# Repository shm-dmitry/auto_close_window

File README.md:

This project allows auto-open and auto-close your windows.
Project consists schematics of 3 modules and firmware for 2 controllers

Project re-started

In-door modules:
==============

1. Placed on window neare handle. It controls handle state (via hall sensor and magnet) and allows to you to push button open or close manually
Also this module connected to WIFI and allows to to control your window from any smart house server (via MQTT protocol).
2. Placed on up-side window frame. Contains servo, receives commands from module#1 and executes it.

Out-door module:
==============

1. Listen for a noise and check air quality. 

Project status
==============

| Hardware | status |
| ---- | ---- |
| Indoor schema :: near-handle module | no |
| Indoor schema :: servo module | no |
| Indoor schema :: digital channel to outdoor schema | no |
| Outdoor module schema :: microcontroller and its periphery | no |
| Outdoor module schema :: sensors | no |

| Board | status |
| ---- | ---- |
| Indoor board :: near-handle module | no |
| Indoor board :: servo module | no |
| Outdoor module board | no |

| Firmware | status |
| ---- | ---- |
| Indoor firmware :: hardware sensors - hall, switch and soft lock | no |
| Indoor firmware :: buttons | no |
| Indoor firmware :: servo control and calibration | no |
| Indoor firmware :: led indication | no |
| Indoor firmware :: controller | no |
| Outdoor firmware :: BMP280 | no |
| Outdoor firmware :: SGP30 | no |
| Outdoor firmware :: Noise sensor | no |
| Outdoor firmware :: Sensor value filters and controller | no |
| Outdoor firmware :: Data transmitter | no |

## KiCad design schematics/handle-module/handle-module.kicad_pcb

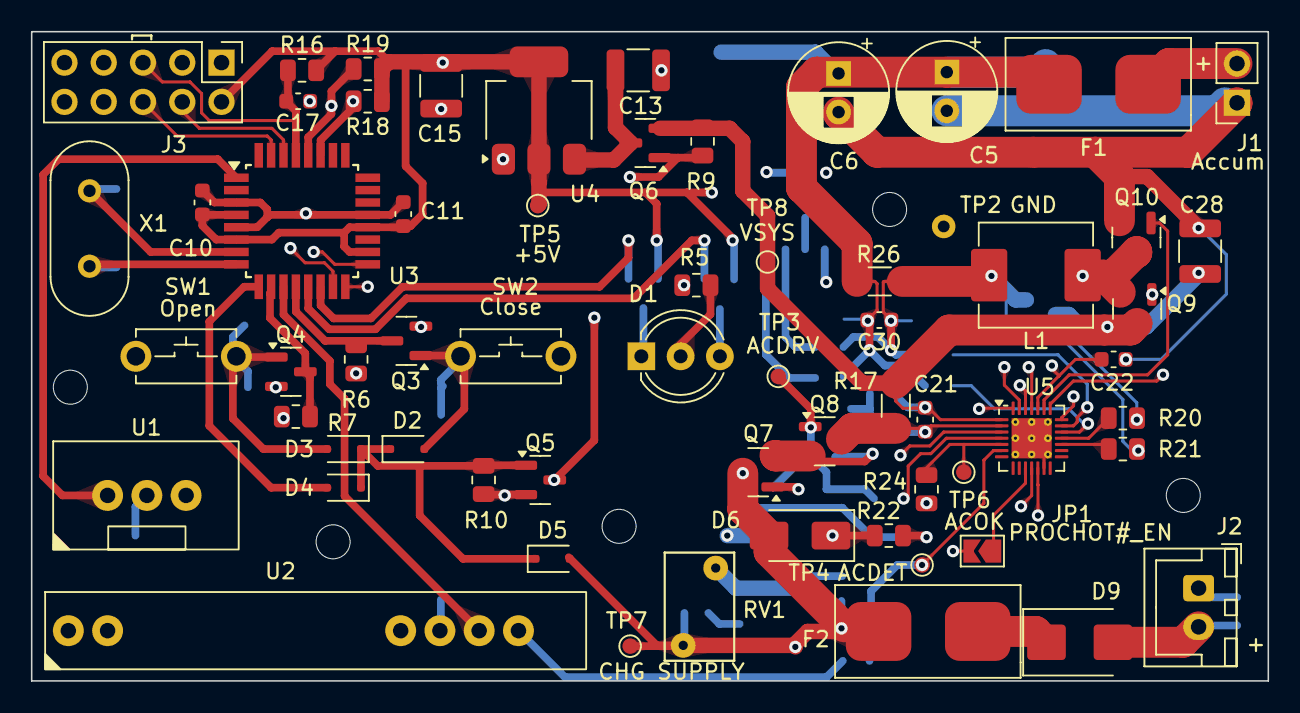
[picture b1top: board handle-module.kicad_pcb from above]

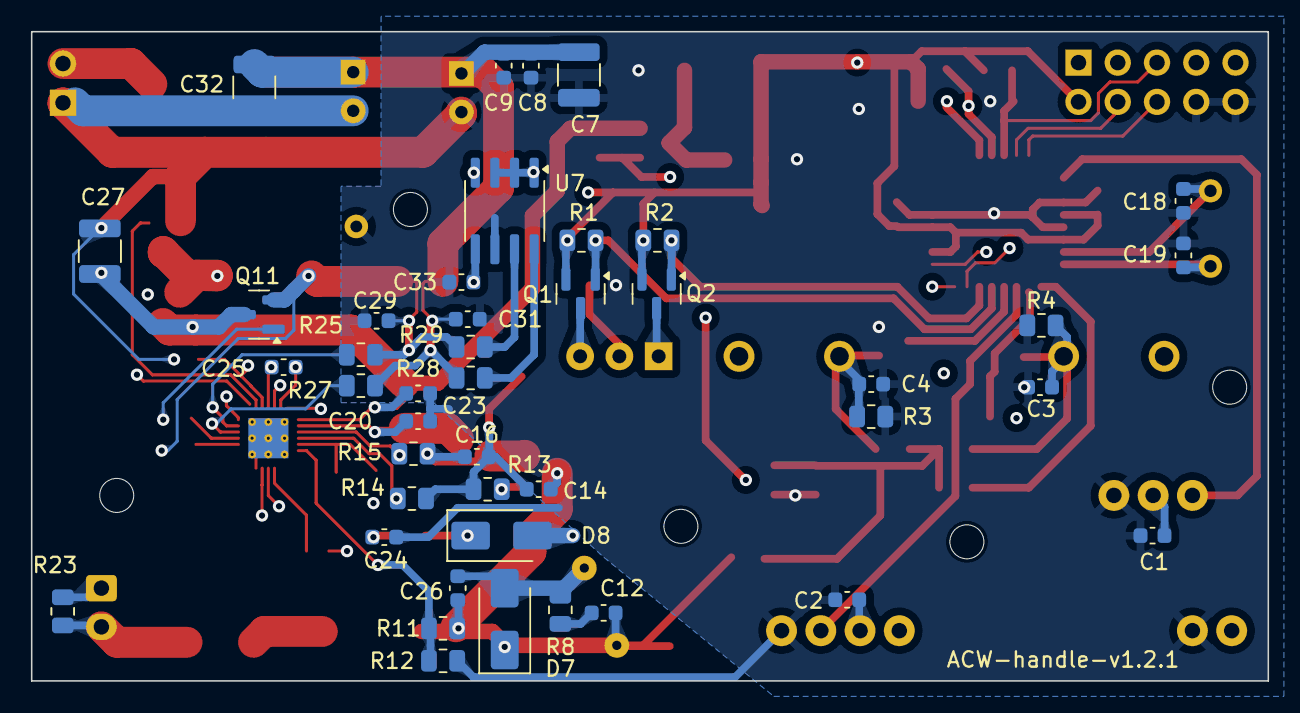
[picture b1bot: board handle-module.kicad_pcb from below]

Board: 4 copper layers, 80.0 x 42.0 mm, 114 parts (43 on the bottom side), 61 nets.

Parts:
C1, C2, C8, C12, C22, C24: 2.2 uF; C_0603_1608Metric
C3, C4, C9, C10, C11, C17, C20, C21, C23, C29, C30, C31, C33: 100 nF; C_0603_1608Metric
C5, C6: 100 uF; CP_Radial_D6.3mm_P2.50mm
C7, C13, C15, C27, C28, C32: 22 uF; C_1210_3225Metric
C14: 1 nF; C_0603_1608Metric
C16, C25: 47 nF; C_0603_1608Metric
C18, C19: 15 pF; C_0603_1608Metric
C26: 4.7 uF; C_0603_1608Metric
D1: red/green, common cathode, F3; LED_D5.0mm-3
D2, D3, D4, D5: BAT760; D_SOD-323F
D6, D8: 15MQ030NPBF; D_SMA
D7: SMAJ26A; D_SMA
D9: ES2J; D_SMB
F1, F2: 3A; FuseHolder1808
H1, H2, H3, H4, H5: MountingHole; MountingHole_2.2mm_M2
J1: 2*LiFePo4@18650@1800mAh, 6,4V; PinSocket_1x02_P2.54mm_Vertical
J2: Charger; JST_XH_B2B-XH-A_1x02_P2.50mm_Vertical
J3: USBASP; PinHeader_2x05_P2.54mm_Vertical
JP1: PROCHOT#_EN; SolderJumper-2_P1.3mm_Open_TrianglePad1.0x1.5mm
L1: AMPLF0630, 8,2uH; L_Abracon_ASPI-0630LR
NT1: AGND/PGND; NetTie-2_SMD_Pad2.0mm
NT2, NT3: NetTie_2; NetTie-2_SMD_Pad0.5mm
Q1, Q2, Q6: IRLML5203; SOT-23
Q3, Q4, Q5, Q7, Q8, Q9, Q10, Q11: IRLML0030; SOT-23
R1, R2, R3, R4, R6, R7, R9, R10, R16, R18, R19, R24: 10K; R_0805_2012Metric
R5: 620; R_0805_2012Metric
R8: 5R; R_0805_2012Metric
R11: 100K; R_0805_2012Metric
R12: 45K; R_0805_2012Metric
R13: 5; R_0805_2012Metric
R14, R15: 3K9; R_0805_2012Metric
R17, R26: 0.01 R; R_1206_3216Metric
R20: 3K3; R_0805_2012Metric
R21, R22, R25, R27, R28, R29: 10; R_0805_2012Metric
R23: 2K2; R_0805_2012Metric
RV1: JVR-05N180M; RV_Disc_D7mm_W4.5mm_P5mm
SW1, SW2: KLS7-TS3601-5.0-180; SW_PUSH_P6.5_W3.5
TP2: GND; TestPoint_Plated_Hole_D1.0mm
TP3: ACDRV; TestPoint_Pad_D1.0mm
TP4: ACDET; TestPoint_Pad_D1.0mm
TP5: +5V; TestPoint_Pad_D1.0mm
TP6: ACOK; TestPoint_Pad_D1.0mm
TP7: CHG SUPPLY; TestPoint_Pad_D1.0mm
TP8: VSYS; TestPoint_Pad_D1.0mm
U1: STX882@443MHz; STX882_Vertical
U2: SRX882@443MHz; SRX882_Vertical
U3: ATmega328-A; TQFP-32_7x7mm_P0.8mm
U4: AMS1117-5.0; SOT-223-3_TabPin2
U5: BQ24780S; QFN-28-1EP_4x4mm_P0.4mm_EP2.6x2.6mm_ThermalVias
U7: INA219; SOIC-8_3.9x4.9mm_P1.27mm
X1: HC-49U, 8MHz; Crystal_HC49-U_Vertical

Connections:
+5V: C1.1, C2.1, C10.1, C11.1, C15.1, C33.1, J3.2, Q1.2 (S), Q2.2 (S), R1.2, R2.2, R6.2, R7.2, R16.2, R18.1, R19.1, R24.2, TP5.1, U1.3 (VCC), U2.3 (VCC), U2.4 (CS), U3.4 (VCC), U3.6 (VCC), U3.18 (AVCC), U3.20 (AREF), U4.2 (VO), U7.5 (VCC)
/CHARGER_BATDRV: Q11.1 (G), R20.1
/CHARGER_BATSRC: C29.1, C30.1, L1.2, NT2.2, Q11.2 (S), R21.1, R26.1
/CHARGER_SRN: NT3.1, R27.1, R28.1
/CHARGER_SRP: NT2.1, R25.2, R29.2
/CHARGER_SUPPLY: C12.1, C14.1, C26.1, D5.2 (A), D6.2 (A), D7.1 (A1), F2.2, Q7.3 (D), R11.1, RV1.1, TP7.1
/CHR_VSYS_NMOS: C16.1, Q7.2 (S), Q8.2 (S), R15.1
/CLOSE_BUTTON: C4.2, D2.2 (A), Q3.1 (G), R3.1, SW2.1
/CLOSE_BUTTON_5V#: Q3.3 (D), R6.1, U3.12 (PB0)
/FM_IN: U2.5 (DATA), U3.11 (PD7)
/FM_OUT: U1.2 (DATA), U3.1 (PD3)
/IC_POWER_UP: D4.2 (A), U3.9 (PD5)
/LED_GREEN#: Q1.1 (G), R1.1, U3.13 (PB1)
/LED_RED#: Q2.1 (G), R2.1, U3.14 (PB2)
/MISO: J3.9, U3.16 (PB4)
/MOSI: J3.1, U3.15 (PB3)
/OPEN_BUTTON: C3.2, D3.2 (A), Q4.1 (G), R4.1, SW1.2
/OPEN_BUTTON_5V#: Q4.3 (D), R7.1, U3.10 (PD6)
/PROCHOT#: JP1.2 (B), Q5.3 (D), Q6.1 (G), R9.2
/RESET#: C17.1, J3.5, R16.1, U3.29 (~RESET/PC6)
/RXD: J3.4, U3.30 (PD0)
/SCK: J3.7, U3.17 (PB5)
/SCL: R19.2, U3.28 (PC5), U5.12 (SCL), U7.4 (SCL)
/SDA: R18.2, U3.27 (PC4), U5.11 (SDA), U7.1 (A1), U7.2 (A0), U7.3 (SDA)
/TXD: J3.6, U3.31 (PD1)
/VBAT: C5.1, C6.1, C7.1, C8.1, C9.2, C30.2, C31.1, C32.1, D8.2 (A), F1.2, NT3.2, R26.2, SW1.1, SW2.2
/VSYS: C21.2, C23.1, C27.1, C28.1, Q6.2 (S), Q9.3 (D), Q11.3 (D), R9.1, R17.2, TP8.1, U5.1 (ACN)
GNDA: C1.2, C2.2, C3.1, C4.1, C6.2, C7.2, C8.2, C9.1, C10.2, C11.2, C13.2, C15.2, C17.2, C18.2, C19.2, C20.2, C23.2, C24.2, C29.2, C31.2, C33.2, J3.8, J3.10, NT1.2, Q3.2 (S), Q4.2 (S), Q5.2 (S), R3.2, R4.2, R5.2, R10.2, R12.2, TP2.1, U1.4 (GND), U2.2 (GND), U2.6 (GND), U3.3 (GND), U3.5 (GND), U3.21 (GND), U4.1 (GND), U5.22 (AGND), U7.6 (GND)
GNDPWR: C5.2, C22.2, C26.2, C27.2, C28.2, C32.2, D7.2 (A2), J1.1, J2.1, NT1.1, Q10.2 (S), R8.2, R23.2, RV1.2, U5.13 (CMPIN), U5.29 (PGND)
unnamed: C12.2, R8.1
unnamed: D1.1 (A1), Q2.3 (D)
unnamed: D1.3 (A2), Q1.3 (D)
unnamed: D1.2 (K), R5.1
unnamed: D2.1 (K), D3.1 (K), D4.1 (K), D5.1 (K), Q5.1 (G), R10.1
unnamed: D6.1 (K), D8.1 (K), R22.2
unnamed: D9.2 (A), J2.2, R23.1
unnamed: D9.1 (K), F2.1
unnamed: F1.1, J1.2
unnamed: JP1.1 (A), U5.10 (PROCHOT#)
unnamed: C13.1, Q6.3 (D), U4.3 (VI)
unnamed: Q7.1 (G), R13.1
unnamed: C20.1, C21.1, Q8.3 (D), R17.1, U5.2 (ACP)
unnamed: C14.2, C16.2, Q8.1 (G), R13.2, R14.1, TP3.1
unnamed: Q9.1 (G), U5.26 (HIDRV)
unnamed: C25.2, L1.1, Q9.2 (S), Q10.3 (D), U5.27 (PHASE)
unnamed: Q10.1 (G), U5.23 (LODRV)
unnamed: C18.1, U3.7 (XTAL1/PB6), X1.2
unnamed: C19.1, U3.8 (XTAL2/PB7), X1.1
unnamed: R11.2, R12.1, TP4.1, U5.6 (ACDET)
unnamed: R14.2, U5.4 (ACDRV)
unnamed: R24.1, TP6.1, U5.5 (ACOK)
unnamed: R20.2, U5.18 (BATDRV)
unnamed: R21.2, U5.17 (BATSRC)
unnamed: C25.1, U5.25 (BTST)
unnamed: R15.2, U5.3 (CMSRC)
unnamed: C22.1, U5.21 (ILIM), U5.24 (REGN)
unnamed: R27.2, U5.19 (SRN)
unnamed: R25.1, U5.20 (SRP)
unnamed: C24.1, R22.1, U5.28 (VCC)
unnamed: R28.2, U7.8 (VIN_+)
unnamed: R29.1, U7.7 (VIN_-)

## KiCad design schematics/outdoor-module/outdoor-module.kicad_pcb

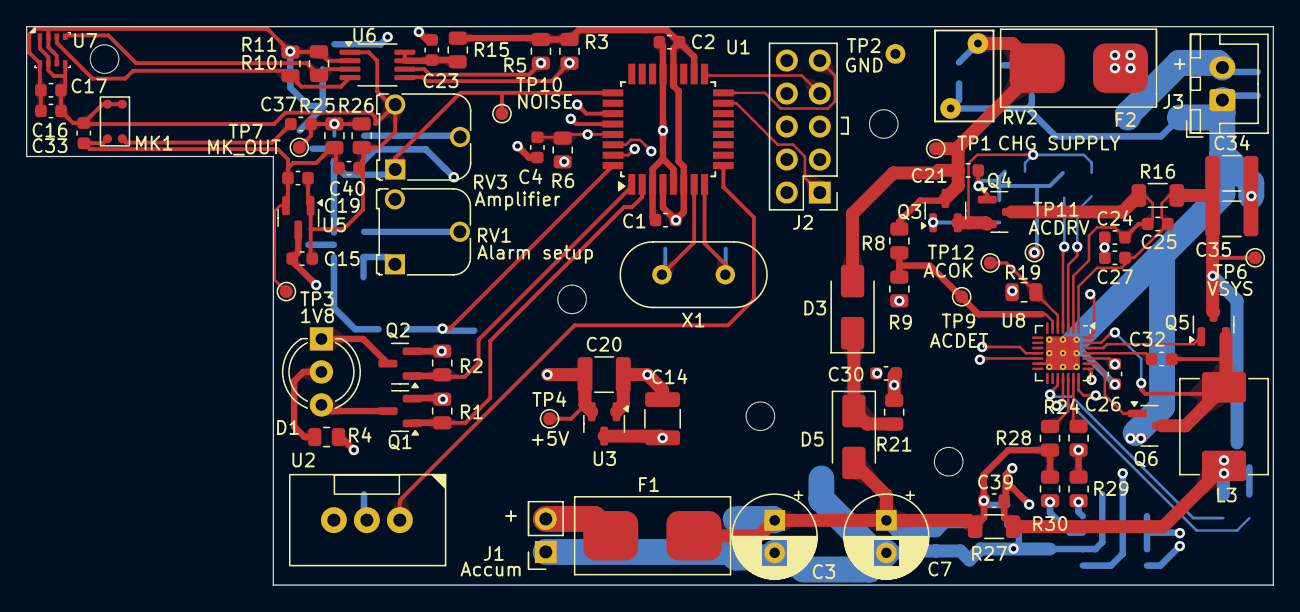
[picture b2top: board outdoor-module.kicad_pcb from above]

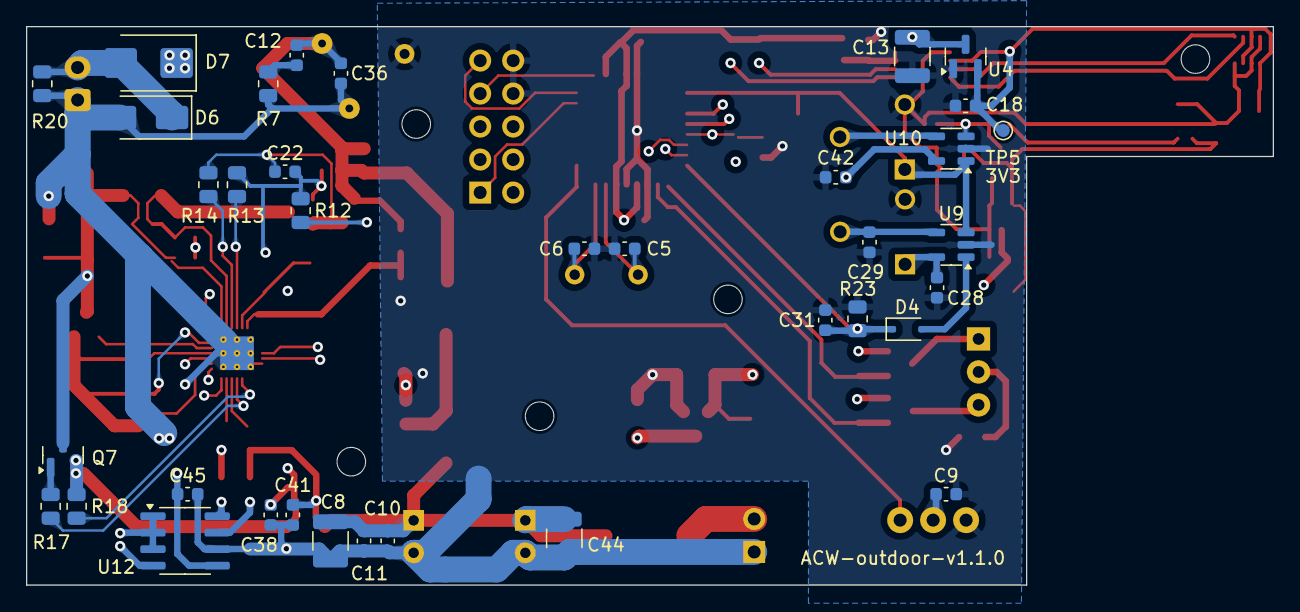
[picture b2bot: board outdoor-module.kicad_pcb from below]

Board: 4 copper layers, 96.0 x 43.0 mm, 127 parts (37 on the bottom side), 63 nets.

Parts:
C1, C2, C4, C9, C11, C16, C17, C24, C25, C27, C28, C29, C31, C33, C37, C38, C39, C40, C41, C42, C45: 100 nF; C_0603_1608Metric
C3, C7: 100 uF; CP_Radial_D6.3mm_P2.50mm
C5, C6: 15 pF; C_0603_1608Metric
C8, C13, C14, C20, C34, C35, C44: 22 uF; C_1210_3225Metric
C10, C15, C18, C19, C30: 1 uF; C_0603_1608Metric
C12, C26: 2.2 uF; C_0603_1608Metric
C21: 1 nF; C_0603_1608Metric
C22, C32: 47 nF; C_0603_1608Metric
C23: 200 pF; C_0603_1608Metric
C36: 4.7 uF; C_0603_1608Metric
D1: red/green, common cathode, F3; LED_D5.0mm-3
D3, D5: 15MQ030NPBF; D_SMA
D4: BAV21WS; D_SOD-323F
D6: SMAJ26A; D_SMA
D7: ES2J; D_SMB
F1, F2: 3A; FuseHolder1808
H1, H2, H3, H4, H5: MountingHole; MountingHole_2.2mm_M2
J1: 2*LiFePo4@18650@1800mAh, 6,4V; PinSocket_1x02_P2.54mm_Vertical
J2: USBASP; PinHeader_2x05_P2.54mm_Vertical
J3: Charger; JST_XH_B2B-XH-A_1x02_P2.50mm_Vertical
L3: AMPLF0630, 8,2uH; L_Abracon_ASPI-0630LR
MK1: VSM3729AT-GL9-A30; SMD03722C4
NT1: AGND/PGND; NetTie-2_SMD_Pad2.0mm
NT2, NT3: NetTie_2; NetTie-2_SMD_Pad0.5mm
Q1, Q2: IRLML5203; SOT-23
Q3, Q4, Q5, Q6, Q7: IRLML0030; SOT-23
R1, R2, R6, R19: 10K; R_0805_2012Metric
R3, R5, R10, R11: 4K7; R_0805_2012Metric
R4: 1K; R_0805_2012Metric
R7: 2; R_0805_2012Metric
R8, R23, R25, R26: 100K; R_0805_2012Metric
R9: 45K; R_0805_2012Metric
R12: 4R7; R_0805_2012Metric
R13, R14, R17: 4K; R_0805_2012Metric
R15: 200K; R_0805_2012Metric
R16, R27: 0.01 R; R_1206_3216Metric
R18, R21, R24, R28, R29, R30: 10; R_0805_2012Metric
R20: 2K2; R_0805_2012Metric
RV1, RV3: RM065, 100K; Potentiometer_Runtron_RM-065_Vertical
RV2: JVR-05N180M; RV_Disc_D7mm_W4.5mm_P5mm
TP1: CHG SUPPLY; TestPoint_Pad_D1.0mm
TP2: GND; TestPoint_Plated_Hole_D1.0mm
TP3: 1V8; TestPoint_Pad_D1.0mm
TP4: +5V; TestPoint_Pad_D1.0mm
TP5: 3V3; TestPoint_Pad_D1.0mm
TP6: VSYS; TestPoint_Pad_D1.0mm
TP7: MK_OUT; TestPoint_Pad_D1.0mm
TP9: ACDET; TestPoint_Pad_D1.0mm
TP10: NOISE; TestPoint_Pad_D1.0mm
TP11: ACDRV; TestPoint_Pad_D1.0mm
TP12: ACOK; TestPoint_Pad_D1.0mm
U1: ATmega328-A; TQFP-32_7x7mm_P0.8mm
U2: STX882@315MHz; STX882_Vertical
U3: MCP1703T-5002E; SOT-23
U4: MCP1703T-3302E; SOT-23
U5: MCP1703T-1802E; SOT-23
U6: PCA9306; MSOP-8_3x3mm_P0.65mm
U7: BME280; Bosch_LGA-8_2.5x2.5mm_P0.65mm_ClockwisePinNumbering
U8: BQ24780S; QFN-28-1EP_4x4mm_P0.4mm_EP2.6x2.6mm_ThermalVias
U9, U10: AD8541; SOT-23-5
U12: INA219; SOIC-8_3.9x4.9mm_P1.27mm
X1: HC-49U, 8MHz; Crystal_HC49-U_Vertical

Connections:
+1V8: C19.1, C33.1, C40.1, MK1.1 (VCC), R25.1, TP3.1, U5.2 (VO)
+3V3: C16.1, C17.1, C18.2, R10.1, R11.1, TP5.1, U4.2 (VO), U6.2 (VREF1), U7.2 (CSB), U7.6 (VDDIO), U7.8 (VDD)
+5V: C1.1, C2.1, C9.1, C13.1, C15.1, C20.1, C28.1, C42.1, C45.1, J2.2, Q1.2 (S), Q2.2 (S), R1.2, R2.2, R3.1, R5.1, R6.2, R15.1, R19.2, RV1.1, TP4.1, U1.4 (VCC), U1.6 (VCC), U1.18 (AVCC), U1.20 (AREF), U2.3 (VCC), U3.2 (VO), U4.3 (VI), U5.3 (VI), U9.5 (V+), U10.5 (V+), U12.5 (VCC)
/CHARGER_BATDRV: Q7.1 (G), R17.1
/CHARGER_BATSRC: C38.1, C39.1, L3.2, NT2.2, Q7.2 (S), R18.1, R27.1
/CHARGER_DONE#: Q1.1 (G), R1.1, U1.2 (PD4)
/CHARGER_IN_PROGRESS#: Q2.1 (G), R2.1, U1.1 (PD3)
/CHARGER_SRN: NT3.1, R28.1, R30.1
/CHARGER_SRP: NT2.1, R24.1, R29.2
/CHARGER_SUPPLY: C12.1, C21.1, C36.1, D3.2 (A), F2.2, Q3.3 (D), R8.1, RV2.1, TP1.1
/FM_OUT: U1.9 (PD5), U2.2 (DATA)
/MISO: J2.9, U1.16 (PB4)
/MOSI: J2.1, U1.15 (PB3)
/NOISE: RV3.1, TP10.1, U1.25 (PC2), U9.3 (Vin+), U10.1 (OUT)
/NOISE_ALARM: C31.1, D4.1 (K), R23.1, U1.32 (PD2)
/RESET#: C4.1, J2.5, R6.1, U1.29 (~RESET/PC6)
/RXD: J2.4, U1.30 (PD0)
/SCK: J2.7, U1.17 (PB5)
/SCL: R5.2, U1.28 (PC5), U6.6 (SCL2), U8.12 (SCL), U12.4 (SCL)
/SCL_3V3: R10.2, U6.3 (SCL1), U7.4 (SCK)
/SDA: R3.2, U1.27 (PC4), U6.5 (SDA2), U8.11 (SDA), U12.1 (A1), U12.2 (A0), U12.3 (SDA)
/SDA_3V3: R11.2, U6.4 (SDA1), U7.3 (SDI)
/TXD: J2.6, U1.31 (PD1)
/VBAT: C3.1, C7.1, C8.1, C10.1, C11.2, C39.2, C41.1, C44.1, D5.2 (A), F1.2, NT3.2, R27.2
/VSYS: C14.1, C25.2, C27.1, C34.1, C35.1, Q5.3 (D), Q7.3 (D), R16.2, TP6.1, U3.3 (VI), U8.1 (ACN)
GNDA: C1.2, C2.2, C4.2, C5.2, C6.2, C7.2, C8.2, C9.2, C10.2, C11.1, C13.2, C14.2, C15.2, C16.2, C17.2, C18.1, C19.2, C20.2, C23.1, C24.2, C27.2, C28.2, C29.2, C30.2, C31.2, C33.2, C38.2, C40.2, C41.2, C42.2, C45.2, J2.8, J2.10, MK1.2 (GND), MK1.3 (GND), NT1.2, R4.2, R9.2, R23.2, R26.2, RV1.3, RV3.3, TP2.1, U1.3 (GND), U1.5 (GND), U1.21 (GND), U2.4 (GND), U3.1 (GND), U4.1 (GND), U5.1 (GND), U6.1 (GND), U7.1 (GND), U7.5 (SDO), U7.7 (GND), U8.22 (AGND), U9.2 (GND), U10.2 (GND), U12.6 (GND)
GNDPWR: C3.2, C26.2, C34.2, C35.2, C36.2, C44.2, D6.2 (A2), J1.1, J3.1, NT1.1, Q6.2 (S), R7.2, R20.2, RV2.2, U8.13 (CMPIN), U8.29 (PGND)
unnamed: C12.2, R7.1
unnamed: D1.1 (A1), Q2.3 (D)
unnamed: D1.3 (A2), Q1.3 (D)
unnamed: D1.2 (K), R4.1
unnamed: D3.1 (K), D5.1 (K), R21.2
unnamed: D4.2 (A), U9.1 (OUT)
unnamed: D6.1 (A1), D7.2 (A), J3.2, R20.1
unnamed: D7.1 (K), F2.1
unnamed: F1.1, J1.2
unnamed: C37.1, MK1.4 (OUT)
unnamed: Q3.1 (G), R12.1
unnamed: C22.1, Q3.2 (S), Q4.2 (S), R14.1
unnamed: C24.1, C25.1, Q4.3 (D), R16.1, U8.2 (ACP)
unnamed: C21.2, C22.2, Q4.1 (G), R12.2, R13.1, TP11.1
unnamed: Q5.1 (G), U8.26 (HIDRV)
unnamed: C32.2, L3.1, Q5.2 (S), Q6.3 (D), U8.27 (PHASE)
unnamed: Q6.1 (G), U8.23 (LODRV)
unnamed: C5.1, U1.7 (XTAL1/PB6), X1.2
unnamed: C6.1, U1.8 (XTAL2/PB7), X1.1
unnamed: C23.2, R15.2, U6.7 (VREF2), U6.8 (EN)
unnamed: R8.2, R9.1, TP9.1, U8.6 (ACDET)
unnamed: R13.2, U8.4 (ACDRV)
unnamed: R19.1, TP12.1, U8.5 (ACOK)
unnamed: R17.2, U8.18 (BATDRV)
unnamed: R18.2, U8.17 (BATSRC)
unnamed: C32.1, U8.25 (BTST)
unnamed: R14.2, U8.3 (CMSRC)
unnamed: C26.1, U8.21 (ILIM), U8.24 (REGN)
unnamed: R28.2, U8.19 (SRN)
unnamed: R24.2, U8.20 (SRP)
unnamed: C30.1, R21.1, U8.28 (VCC)
unnamed: C29.1, RV1.2, U9.4 (Vin-)
unnamed: C37.2, R25.2, R26.1, TP7.1, U10.3 (Vin+)
unnamed: RV3.2, U10.4 (Vin-)
unnamed: R29.1, U12.8 (VIN_+)
unnamed: R30.2, U12.7 (VIN_-)

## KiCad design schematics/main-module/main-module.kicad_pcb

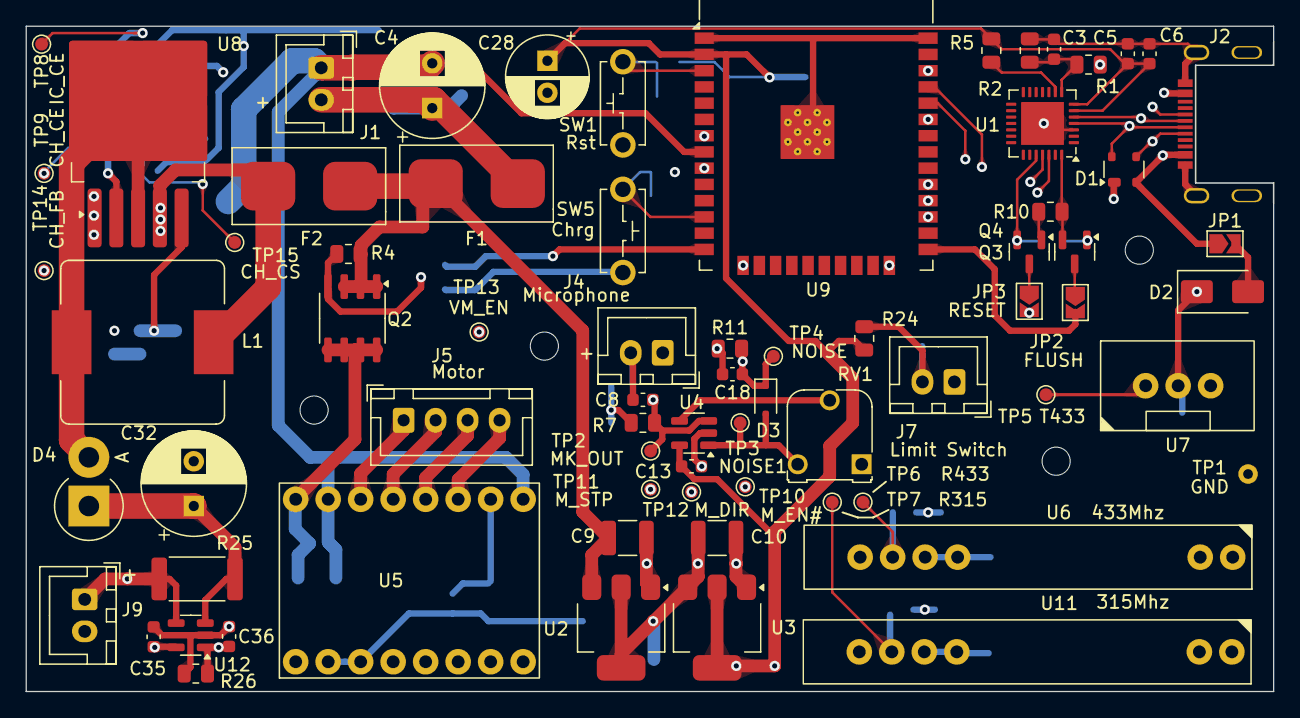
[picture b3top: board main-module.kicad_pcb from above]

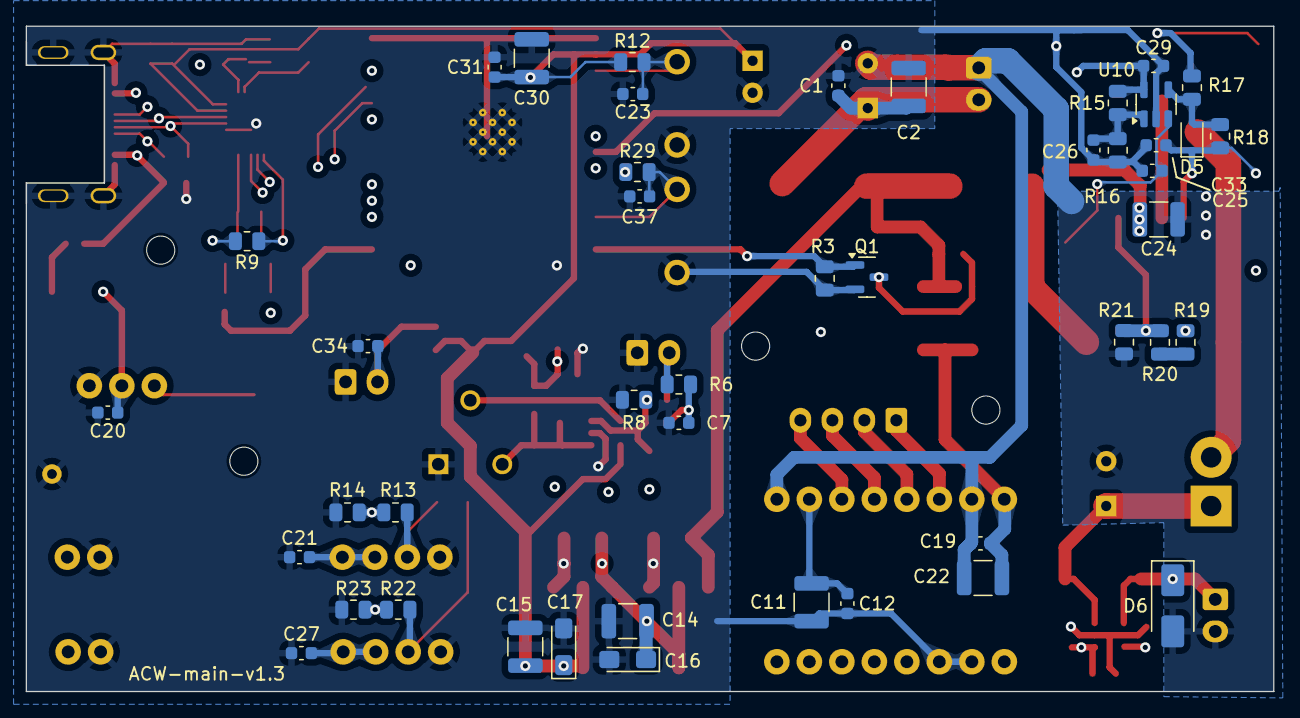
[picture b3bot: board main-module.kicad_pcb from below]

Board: 4 copper layers, 97.5 x 52.0 mm, 121 parts (45 on the bottom side), 55 nets.

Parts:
C1, C12, C19, C20, C21, C27, C31: 4.7 uF; C_0603_1608Metric
C2, C9, C10, C11, C14, C15, C22, C24, C30: 22 uF; C_1210_3225Metric
C3, C5, C6, C33: 10 uF; C_0603_1608Metric
C4: 1000 uF; CP_Radial_D8.0mm_P3.50mm
C7, C13, C29, C35: 100 nF; C_0603_1608Metric
C8: 47 nF; C_0603_1608Metric
C16, C17: 22 uF; CP_EIA-3216-10_Kemet-I_Pad1.58x1.35mm_HandSolder
C18: 1 uF; C_0603_1608Metric
C23, C34, C37: 330 nF; C_0603_1608Metric
C25, C26, C36: 10 nF; C_0603_1608Metric
C28: 100 uF; CP_Radial_D6.3mm_P2.50mm
C32: 220 uF@35V; CP_Radial_D8.0mm_P3.50mm
D1: SP0503BAHT; SOT-143
D2: US1M; D_SMA
D3, D5: BAV21WS; D_SOD-323F
D4: SR540; D_DO-201AD_P3.81mm_Vertical_AnodeUp
D6: SMAJ26A; D_SMA
F1: 6A; FuseHolder1808
F2: 3A; FuseHolder1808
H1, H2, H3, H4: MountingHole; MountingHole_2.2mm_M2
J1: Conn_01x02_Socket; JST_XH_B2B-XH-A_1x02_P2.50mm_Vertical
J2: USB_C_Receptacle_USB2.0; USB_C_P16_MIDMOUNT_1.6
J4: Microphone; JST_XH_B2B-XH-A_1x02_P2.50mm_Vertical
J5: Conn_01x04_Socket; JST_XH_B4B-XH-A_1x04_P2.50mm_Vertical
J7: Limit Switch; JST_XH_B2B-XH-A_1x02_P2.50mm_Vertical
J9: Charger port; JST_XH_B2B-XH-A_1x02_P2.50mm_Vertical
JP1: Charge from flusher; SolderJumper-2_P1.3mm_Open_TrianglePad1.0x1.5mm
JP2: FLUSH; SolderJumper-2_P1.3mm_Open_TrianglePad1.0x1.5mm
JP3: RESET; SolderJumper-2_P1.3mm_Open_TrianglePad1.0x1.5mm
L1: AMPLF1260, 4.7 uH; L_TaiTech_TMPC1265_13.5x12.5mm
NT1: AGND/PGND; NetTie-2_SMD_Pad2.0mm
Q1: IRLML0030; SOT-23
Q2: IRF7425PbF; SOIC-8_3.9x4.9mm_P1.27mm
Q3, Q4: BC847; SOT-23
R1, R13, R22: 22K; R_0805_2012Metric
R2, R14, R23: 47K; R_0805_2012Metric
R3, R6, R8, R9, R10, R11, R15, R20, R24, R29: 10K; R_0805_2012Metric
R4, R5, R12, R19, R21: 1K; R_0805_2012Metric
R7: 20K; R_0805_2012Metric
R16: 200; R_0805_2012Metric
R17: 620; R_0805_2012Metric
R18: 200K; R_0805_2012Metric
R25: 0,5; R_2512_6332Metric
R26: 100K; R_0805_2012Metric
RV1: RM065, 100K; Potentiometer_Runtron_RM-065_Vertical
SW1, SW5: KLS7-TS3601-5.0-180; SW_PUSH_P6.5_W3.5
TP1: GND; TestPoint_Plated_Hole_D1.0mm
TP2: MK_OUT; TestPoint_Pad_D1.0mm
TP3: NOISE1; TestPoint_Pad_D1.0mm
TP4: NOISE; TestPoint_Pad_D1.0mm
TP5: T433; TestPoint_Pad_D1.0mm
TP6: R433; TestPoint_Pad_D1.0mm
TP7: R315; TestPoint_Pad_D1.0mm
TP8: IC_CE; TestPoint_Pad_D1.0mm
TP9: CH_CE; TestPoint_Pad_D1.0mm
TP10: M_EN#; TestPoint_Pad_D1.0mm
TP11: M_STP; TestPoint_Pad_D1.0mm
TP12: M_DIR; TestPoint_Pad_D1.0mm
TP13: VM_EN; TestPoint_Pad_D1.0mm
TP14: CH_FB; TestPoint_Pad_D1.0mm
TP15: CH_CS; TestPoint_Pad_D1.0mm
U1: CP2102N-Axx-xQFN28; QFN-28-1EP_5x5mm_P0.5mm_EP3.35x3.35mm
U2: AMS1117-5.0; SOT-223-3_TabPin2
U3: AMS1117-3.3; SOT-223-3_TabPin2
U4: AD8541; SOT-23-5
U5: TMC2209_Module; TMC2209
U6: SRX882@433Mhz; SRX882_Vertical
U7: STX882@433Mhz; STX882_Vertical
U8: XL6009; TO-263-5_TabPin3
U9: ESP32-WROOM-32
U10: TL331; SOT-23-5
U11: SRX882@315Mhz; SRX882_Vertical
U12: INA169; SOT-23-5

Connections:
+3V3: C5.1, C6.1, C11.2, C12.1, C13.1, C15.2, C17.1, C28.1, C30.2, C31.1, R5.2, R12.1, R24.1, R29.1, U1.6 (VDD), U1.7 (VREGIN), U3.2 (VO), U4.5 (V+), U5.15 (VIO), U9.2 (VDD)
+5V: C7.1, C10.2, C14.2, C16.1, C20.1, C21.1, C27.1, C29.1, C35.1, D2.1 (K), R6.2, R7.2, R15.2, U2.2 (VO), U3.3 (VI), U6.3 (VCC), U6.4 (CS), U7.3 (VCC), U10.5 (V+), U11.3 (VCC), U11.4 (CS), U12.5 (V+)
+7.5V: C9.2, F1.2, F2.1, Q2.1 (S), Q2.2 (S), Q2.3 (S), R4.1, U2.3 (VI)
/7.5V_BEFORE_FUSE: C1.1, C2.1, C4.1, F1.1, J1.2
/+7.5V_CHARGER_AFTER_FUSE: C24.2, F2.2, L1.2, U8.4 (VIN)
/CHARGER_CURRENT_SENCE: C25.2, C36.2, R26.2, TP15.1, U10.3 (+), U12.1
/CHARGER_ENABLE: C33.2, D5.1 (K), R18.1, TP9.1, U8.2 (EN)
/CHARGER_FEEDBACK: R20.1, R21.2, TP14.1, U8.5 (FB)
/CHARGER_START_BUTTON: C37.1, R29.2, SW5.1, U9.12 (IO27)
/D+: D1.4 (K), J2.A6 (D+), J2.B6 (D+), U1.4 (D+)
/D-: D1.3 (K), J2.A7 (D-), J2.B7 (D-), U1.5 (D-)
/ESP32_ENABLE: C23.1, JP3.2 (B), R12.2, SW1.2, U9.3 (EN)
/ESP32_FLUSH: JP2.2 (B), U9.25 (IO0)
/FM_IN_5V_315: R22.2, TP7.1, U11.5 (DATA)
/FM_IN_5V_433: R13.2, TP6.1, U6.5 (DATA)
/FM_IN_315: R22.1, R23.2, U9.33 (IO21)
/FM_IN_433: R13.1, R14.2, U9.29 (IO5)
/FM_OUT_433: TP5.1, U7.2 (DATA), U9.36 (IO22)
/IC_CHARGER_ENABLE: R17.2, TP8.1, U9.8 (IO32)
/LIMIT_SWITCH: C34.1, J7.2, R24.2, U9.9 (IO33)
/M_DIR: TP12.1, U5.8 (DIR), U9.27 (IO16)
/M_ENABLE#: TP10.1, U5.1 (ENABLE#), U9.24 (IO2)
/M_STEP: TP11.1, U5.7 (STEP), U9.28 (IO17)
/NOISE: C18.1, D3.1 (K), R11.2, TP4.1, U9.7 (IO35)
/RXD_3V3: U1.26 (TXD), U9.34 (RXD0/IO3)
/TXD_3V3: U1.25 (RXD), U9.35 (TXD0/IO1)
/VM_ENABLE: Q1.1 (G), R3.1, TP13.1, U9.14 (IO12)
GNDA: C1.2, C2.2, C3.2, C4.2, C5.2, C6.2, C7.2, C9.1, C10.1, C11.1, C12.2, C13.2, C14.1, C15.1, C16.2, C17.2, C18.2, C20.2, C21.2, C23.2, C25.1, C26.1, C27.2, C28.2, C29.2, C30.1, C31.2, C33.1, C34.2, C35.2, C36.1, C37.2, D1.1 (A), J2.A1 (GND), J2.A12 (GND), J2.B1 (GND), J2.B12 (GND), J2.S1 (SHIELD), J4.1, J7.1, NT1.2, Q1.2 (S), R2.2, R3.2, R8.1, R11.1, R14.1, R16.1, R23.1, R26.1, RV1.1, SW1.1, SW5.2, TP1.1, U1.3 (GND), U1.29 (GND), U2.1 (GND), U3.1 (GND), U4.2 (GND), U5.2 (MS1), U5.3 (MS2), U6.2 (GND), U6.6 (GND), U7.4 (GND), U9.1 (GND), U9.15 (GND), U9.38 (GND), U9.39 (GND), U10.2 (V-), U11.2 (GND), U11.6 (GND), U12.2 (GND)
GNDPWR: C19.1, C22.1, C24.1, C32.2, D6.2 (A2), J1.1, J9.2, NT1.1, R21.1, U5.10 (GND), U5.16 (GND), U8.1 (GND)
unnamed: D2.2 (A), JP1.2 (B)
unnamed: D3.2 (A), RV1.3, TP3.1, U4.1 (OUT)
unnamed: D4.2 (A), L1.1, U8.3 (SW)
unnamed: C32.1, D4.1 (K), R19.2, R25.1, U12.3 (+)
unnamed: D5.2 (A), R17.1, R18.2, U10.4
unnamed: D6.1 (A1), J9.1, R25.2, U12.4 (-)
unnamed: C8.1, J4.2, R6.1
unnamed: J5.1, U5.11 (M1B)
unnamed: J5.2, U5.12 (M1A)
unnamed: J5.3, U5.13 (M2A)
unnamed: J5.4, U5.14 (M2B)
unnamed: JP2.1 (A), Q3.3 (C)
unnamed: JP3.1 (A), Q4.3 (C)
unnamed: Q1.3 (D), Q2.4 (G), R4.2
unnamed: Q3.1 (B), R9.2
unnamed: Q3.2 (E), R10.1, U1.28 (~DTR)
unnamed: Q4.1 (B), R10.2
unnamed: Q4.2 (E), R9.1, U1.24 (~RTS)
unnamed: R19.1, R20.2
unnamed: C3.1, R1.2, R2.1, U1.8 (VBUS)
unnamed: R5.1, U1.9 (~RST)
unnamed: C8.2, R7.1, R8.2, TP2.1, U4.3 (Vin+)
unnamed: RV1.2, U4.4 (Vin-)
unnamed: C26.2, R15.1, R16.2, U10.1 (-)
VBUS: D1.2 (K), J2.A4 (VBUS), J2.A9 (VBUS), J2.B4 (VBUS), J2.B9 (VBUS), JP1.1 (A), R1.1
VD: C19.2, C22.2, Q2.5 (D), Q2.6 (D), Q2.7 (D), Q2.8 (D), U5.9 (VM)

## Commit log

2021-07-27 Continue working under schematics
2021-07-27 Added driver for servo FS5103B
2021-07-29 working under schematics
2021-08-03 1. working under schematics. 2. ESP32 firmware writen but not tested yet. 3. I conntected to ATMega controller and uploaded test firmware to it
2021-08-03 stop servo on full-open and full-close positions
2021-08-04 Start debugging process
2021-08-04 Indoor modules schematics and firmware works now!
2021-08-05 Preparing to debug ATMega controller. I have no JTAG, and USBasp does not allows debugging. I will try to use 443 MHZ transmitter and 433 Mhz receiver on raspberry pi as debug terminal :)
2021-08-08 Start writing firmware for outdoor module
2021-08-13 SGP30 Module works now
2021-08-13 I checked several pins_arduino.h, but only this works fine. Thanks to https://github.com/MCUdude/MightyCore
2021-08-13 Remove unused file
2021-08-17 actualized schematics of outdoor noise sensor module
2021-08-17 actualized some nominals in schematics
2021-08-22 BMP280 works now
2021-09-26 Changed Noise sensor schematics. Removed MSGEQ7 chip (replaced with program FFT). I cant find any live. Changed Volume Amplifier from transistors to chio.
2021-09-26 Noise sensor works
2021-09-27 added initially code for filter and encrypter components
2021-10-30 changed schematics. Removed 433MHZ transmitter. Outdoor module will transfer data using ESP32
2021-10-30 Added code to send data from AVR to ESP32
2021-10-30 Estabilished connection between AVR and ESP32. ESP32 ready to read data from AVR and send it into MQTT
2021-10-31 Change noise sensor schema
2021-11-04 changed microcontroller to ATMEGA328P to reduce device size
2021-11-04 Added TX and RX links from USBASP to ATMEGA
2021-11-04 Firmware and ATMega connection are synchronized. USBasp works successfully
2021-11-04 full schema on atmega328 tested and worked
2021-11-05 Start boards preparing - actualized new element dimentions
2021-11-05 Touch sensor are unstable. I made a decision to replace it by normally-open buttons
2021-11-06 Added button borders and nominals
2021-11-07 Start working under first border
2021-11-07 Board redesigned to reduce it width
2021-11-07 Indoor board - ready
2021-11-07 Indoor board - added ground polygon
2021-11-07 Start working under second border
2021-11-08 Servo module ready, but i will change connectors
2021-11-08 Servo module - added holes
2021-11-08 Added board for outdoor module
2021-11-08 Connectors changed
2021-11-08 Fixed issue in one border - all supply lines now connected to capacity only. And from filter capacity power goes to another elements.
2021-11-08 Increased supply line size to servo
2021-11-08 Outdoor module board size reduced
2021-11-08 Changes in library
2021-11-09 Start preparing to order boards. Checked all labels
2021-11-09 Boards checked and ready to order
2021-11-09 Holes moved away from board border
2021-12-17 Touchpad driver replaced by buttons driver.
2021-12-17 Removed unused constants. Updated eagle library
2021-12-17 hear handle module & indoor servo module assembled and checked
2021-12-17 fixed error in outdoor board and schema
2021-12-17 actualized voltage regulator nominal
2021-12-18 Added 3D models
2021-12-19 3D models for box
2021-12-21 Updated 3D models
2021-12-23 Continue working under 3D models
2021-12-24 3D models
2021-12-25 Fixed errors in 3D model connector betwween servo handler and window
2021-12-29 changes in 3D models
2021-12-29 removed test models
2021-12-30 fixed error in servo box
2021-12-31 Ok, I think I finished with indoor 3D models. Outdoor box printing reuqired.
2023-08-22 Project re-startefd
2023-08-23 start create schematics
2023-09-11 Creating schematics and boards
2023-09-12 Second board
2023-09-12 changes in second board
2023-11-02 Project prepared to order
2023-11-29 first version of main-module firmware. not tested yet.
2023-11-29 Encryption code moved from my another project
2023-11-29 I readed 1527 code... in bit-form, but it works.
2023-11-30 FM debugging - intermediate result
2023-12-01 Transmitter/receiver are stable
2023-12-01 assigned different addresses
2023-12-01 added 2 addresses for charger process
2023-12-01 charger tested
2023-12-01 WIFI & NQTT integration
2023-12-01 MQTT integration
2023-12-05 1. start working under handle module; 2. rewrite stepper driver
2023-12-05 Led integration in handle-module
2023-12-06 stepper driver re-writed
2023-12-06 range-checks and define constants in stepper
2023-12-08 Working under firmwares
2023-12-08 HM and MM starts to try work together
2023-12-11 1. first 3D models, 2. charger works
2023-12-11 change nominal
2023-12-13 Working under 3d models
2023-12-14 1. Fixed schema - limit switch connection moved to ADC pin
2023-12-18 Working under firmware
2023-12-25 Prepare to fix error with window position
2023-12-25 several models updated
2023-12-26 firmware works (at least I think so)
2024-01-07 Adjust models to my window
2024-03-07 models
2024-04-05 prepare to rewrite charing schema
2024-04-09 1. board: added protection against high noise in case of endstop is broken. 2. board: added step-up 7.5V -> 15V for charger. 3. firmware - added support for noise protection and some changes in stepp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
2024-04-09 few comments in source code
2024-04-09 added deglich in noise protection.
2024-04-10 Firmware uploaded and tested on the board (without noise sensor at this moment)
2024-04-11 1. added OTA; 2. debug log messages removed from release build using additional flag
2024-05-11 another iteration for outdorr and handle modules
2024-05-14 removed blind vias - it's production is too expensive
2024-07-24 charger (logic path) works normally
2024-07-24 added 'limit switch connected' logic
2024-07-25 noise alarm changes after hardware test
2024-07-25 remove lock file from repository
2024-07-26 firmware adapted to new hardware
2024-07-26 start debugging fm@315 on mm-side
2024-08-28 handle module & main module almost done
2024-08-29 prepare to change ADC working mode to continuus
2024-09-02 ADC logic changed from opeshot to async continuos. This change stabilazed limit switch logic.
2024-09-12 i found problems with 315MHZ freq (some transmitter blocks air near me). So I added another remote control and I will create box for it
2024-09-16 Fixes in models
2024-09-23 adding auto-hide mechanics allows to remove lock mechanizm from window way in unlocked state
2024-10-02 changes in firmware; changes in 3D models
2024-10-02 updated status message topics, updated my configuration example
2024-10-03 added ability to stop processing PDU messages in case of someone wants to spam the air
2024-10-03 drill template fixed
2024-10-09 3D models re-exported
2024-10-14 1. publish initial state after startup; 2. changes in 3D model after testing
2024-11-01 change mm-box to use power cabel
2024-11-01 fix PDU buttons mapping
2024-11-05 before plate update
2024-11-05 change holes in plate
2024-11-12 processing pre-release check, models updated
2024-11-22 added ability to enable/disable steppers on endstop positions
